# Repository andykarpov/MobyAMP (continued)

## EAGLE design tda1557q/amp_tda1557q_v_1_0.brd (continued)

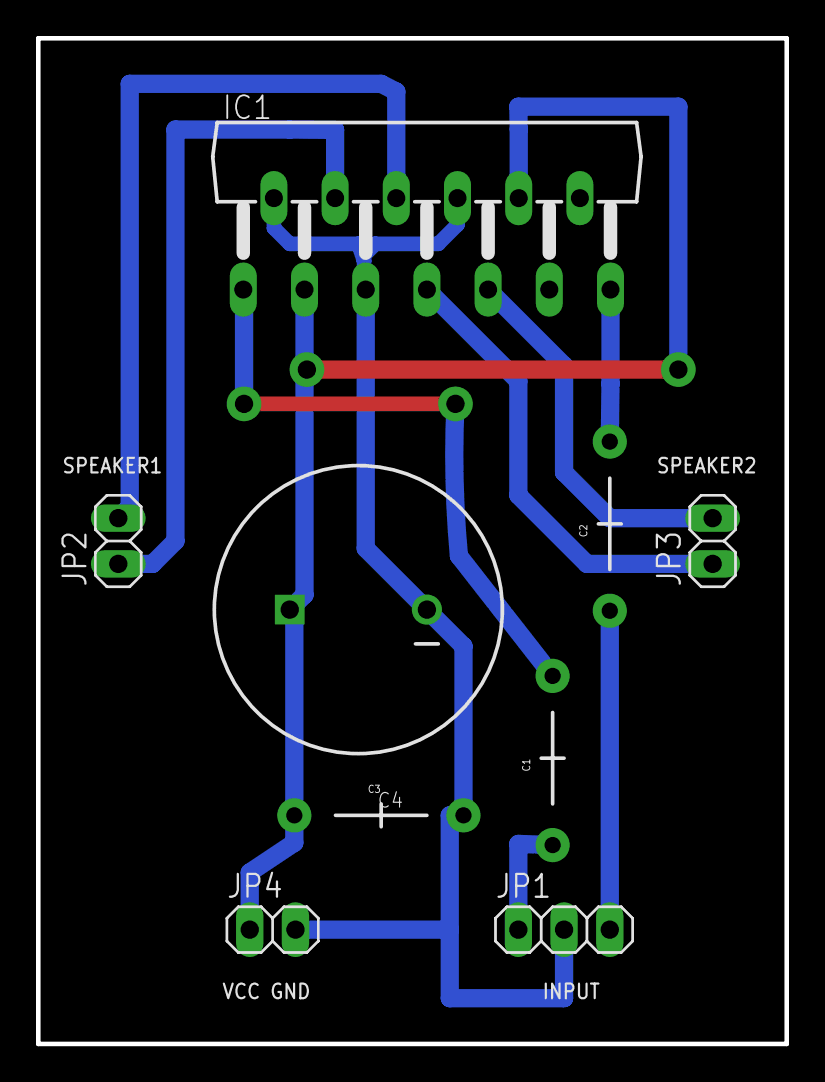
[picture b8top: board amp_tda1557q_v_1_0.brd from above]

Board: 2 copper layers, 41.6 x 55.9 mm, 10 parts (0 on the bottom side), 10 nets.

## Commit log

2013-04-03 Added readme file with library dependencies
2013-04-03 Added a basic README
2013-04-03 Reduced number of EEPROM write cycles, added non-saved settings indication
2013-04-03 Added custom eagle libraries
2013-04-14 Added new simple summator
2013-06-18 Added msgeq7 and pt2322 boards, updated firmware to work with these boards
2013-06-20 Removed init delay
2013-12-30 Latest changes in the working copy
2013-12-30 project cleanup (removed all unused boards / libraries / resources)
2019-02-19 Added interface board for 20x4 lcd, improved firmware for 20x4, refactored pt2322 board
2019-02-20 Improvements for 20x4 interface version
2019-02-28 Fixed tons of small bugs, switched to NewEncoder library, etc
2019-02-28 Latest atmega binary
2019-03-12 latest changes: fixed mute on/off
2019-04-13 Added input source switcher on PCF8574 + 74HC4051
2019-04-29 added mono/stereo switches
2019-04-30 bugfixes, reorganized menus and analog buttons control
2019-05-05 Added Reverse Stereo switch, fixed mute
2019-12-25 a lot of new features, including brightness control
2019-12-25 reverted board on TDA8425
2019-12-25 cleanup
